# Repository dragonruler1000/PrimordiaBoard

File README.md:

</br>
# [Primordiaboard](https://primordiasystems.minecraftchest2.us/projects/primordiaboard.html)

Hello! This is my submission for Hackpad! It was made for Hackpad v3.

## Features
- A big 0.91" OLED screen
- Some custom silkscreen art
- 12 full MX-style keyswitches
- KMK firmware support!

## PCB

Here are pictures of my PCB:

| **Schematic** | **PCB** |
|---------------|---------|
|  |  |

✅ DRC was run with **0 errors**

## CAD

Designed using **FreeCAD** and **TinkerCAD** (it was painful...).

The case fits together with 4x M3 screws and bolts.

## Firmware

The firmware is written in **KMK** and included in this repo.

> ⚠️ There may be additional setup required for KMK—see [KMK Docs](https://kmkfw.io/docs/) for more info.

## Bill of Materials (BOM)
- 1x Seeed XIAO RP2040
- 12x MX-style keyswitches
- 12x 1N4148 diodes
- 1x SSD1306 128x32 OLED (5V VCC, 3.3V logic, I2C)
- 4x M3x16mm screws
- 4x M3 heat-set inserts (5mm x 4mm)
- 1x 3D printed

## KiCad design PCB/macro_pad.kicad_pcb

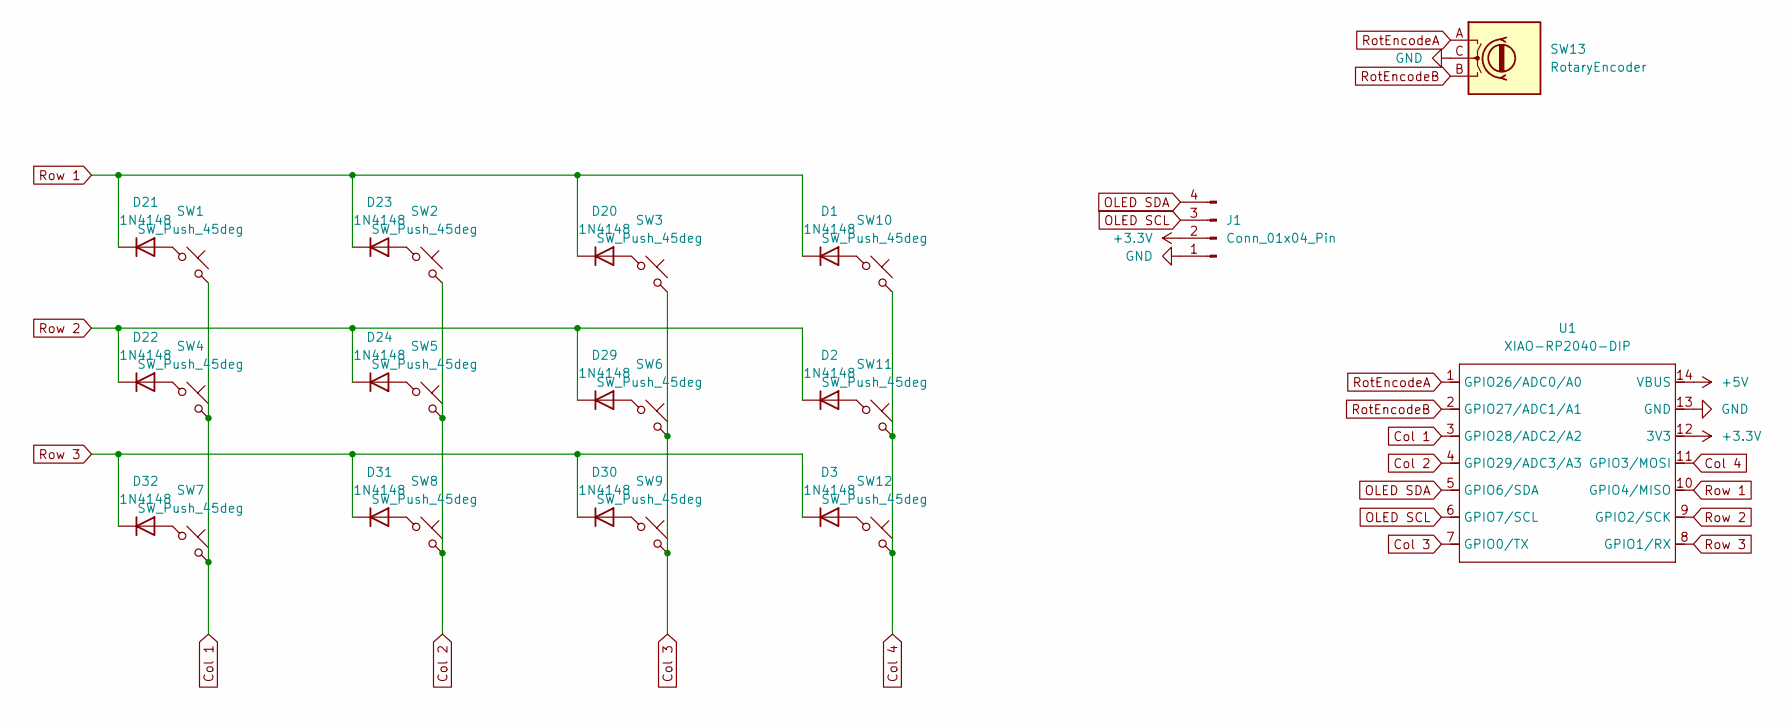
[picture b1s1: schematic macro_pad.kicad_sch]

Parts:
D1, D2, D3, D20, D21, D22, D23, D24, D29, D30, D31, D32: 1N4148; D_DO-35_SOD27_P7.62mm_Horizontal
J1: Conn_01x04_Pin; SSD1306-0.91-OLED-4pin-128x32
SW1, SW2, SW3, SW4, SW5, SW6, SW7, SW8, SW9, SW10, SW11, SW12: SW_Push_45deg; SW_Cherry_MX_1.00u_PCB
SW13: RotaryEncoder; RotaryEncoder_Alps_EC11E_Vertical_H20mm
U1: XIAO-RP2040-DIP

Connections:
+3.3V: J1.2, U1.12 (3V3)
+5V: U1.14 (VBUS)
Col 1: SW1.2, SW4.2, SW7.2, U1.3 (GPIO28/ADC2/A2)
Col 2: SW2.2, SW5.2, SW8.2, U1.4 (GPIO29/ADC3/A3)
Col 3: SW3.2, SW6.2, SW9.2, U1.7 (GPIO0/TX)
Col 4: SW10.2, SW11.2, SW12.2, U1.11 (GPIO3/MOSI)
GND: J1.1, SW13.C, U1.13 (GND)
unnamed: D1.2 (A), SW10.1
unnamed: D2.2 (A), SW11.1
unnamed: D3.2 (A), SW12.1
unnamed: D20.2 (A), SW3.1
unnamed: D21.2 (A), SW1.1
unnamed: D22.2 (A), SW4.1
unnamed: D23.2 (A), SW2.1
unnamed: D24.2 (A), SW5.1
unnamed: D29.2 (A), SW6.1
unnamed: D30.2 (A), SW9.1
unnamed: D31.2 (A), SW8.1
unnamed: D32.2 (A), SW7.1
OLED SCL: J1.3, U1.6 (GPIO7/SCL)
OLED SDA: J1.4, U1.5 (GPIO6/SDA)
RotEncodeA: SW13.A, U1.1 (GPIO26/ADC0/A0)
RotEncodeB: SW13.B, U1.2 (GPIO27/ADC1/A1)
Row 1: D1.1 (K), D20.1 (K), D21.1 (K), D23.1 (K), U1.10 (GPIO4/MISO)
Row 2: D2.1 (K), D22.1 (K), D24.1 (K), D29.1 (K), U1.9 (GPIO2/SCK)
Row 3: D3.1 (K), D30.1 (K), D31.1 (K), D32.1 (K), U1.8 (GPIO1/RX)

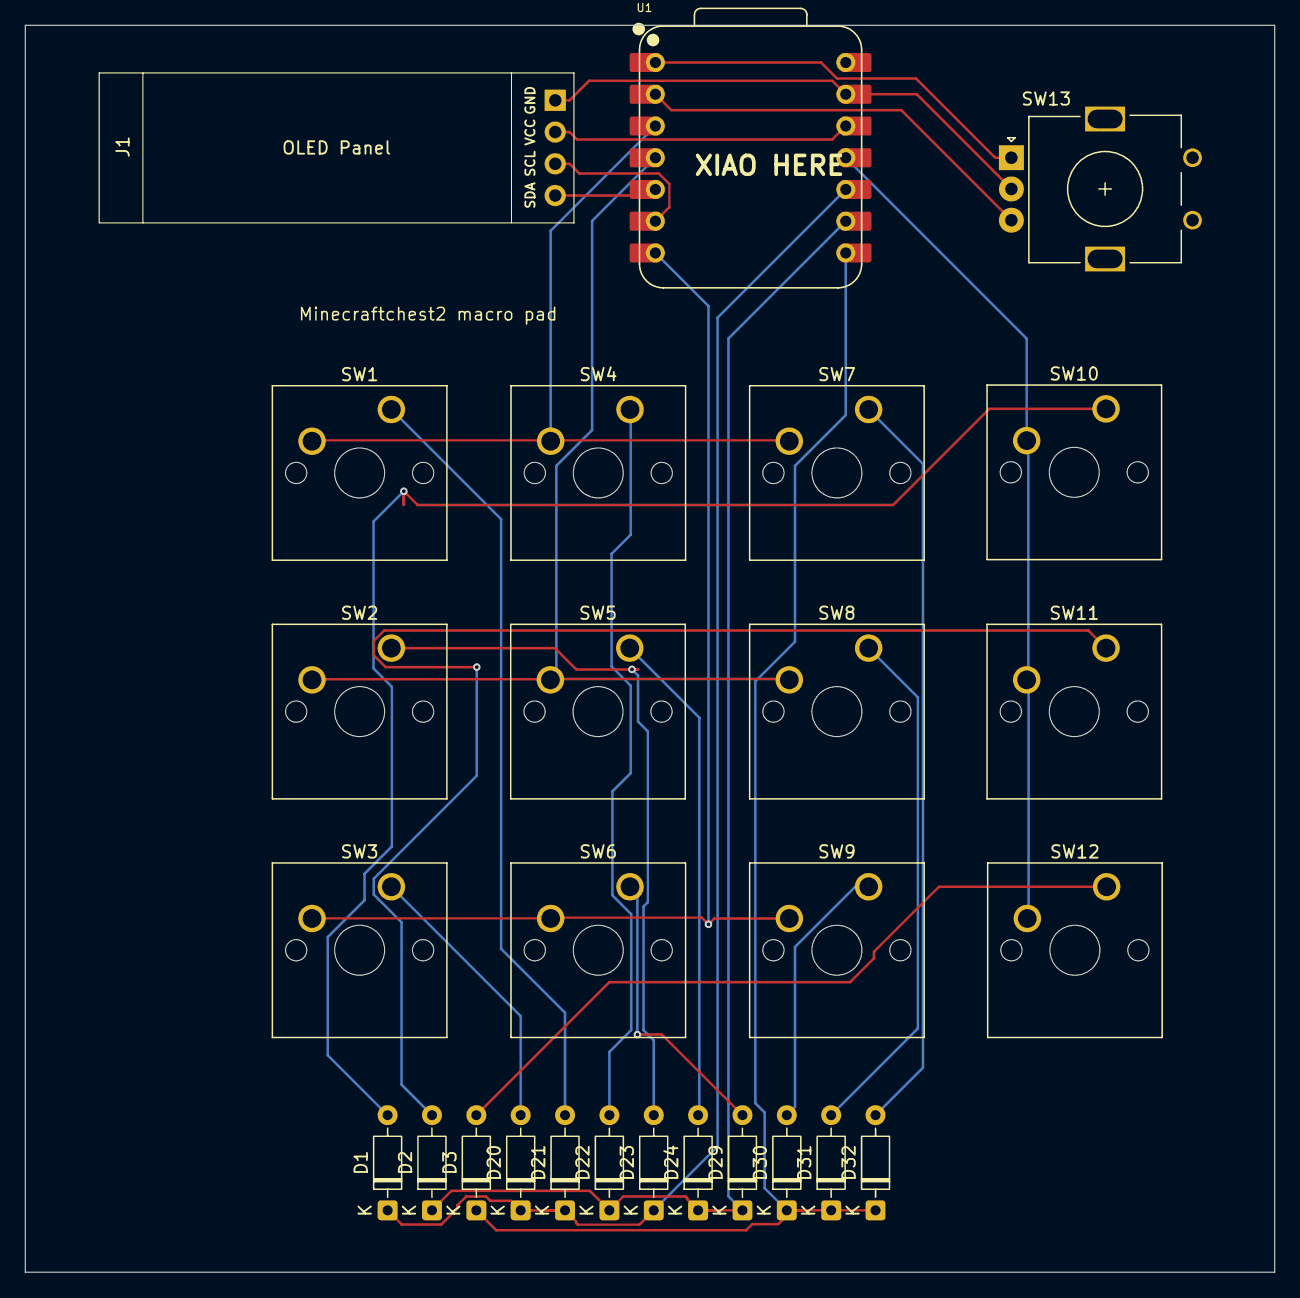
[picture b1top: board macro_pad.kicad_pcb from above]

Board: 2 copper layers, 100.0 x 99.8 mm, 27 parts (0 on the bottom side), 25 nets.

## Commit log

2025-06-07 Started laying out PCB
2025-06-07 Got the traces routed
2025-06-07 adding silk screen and created the gerbers
2025-06-07 added a stl and step version of the pcb
2025-06-10 Got the case for the PCB made
2025-06-14 making sure the case is how i need it.
2025-06-14 adding updated screenshots for the readme
2025-06-15 making sire the needed files are added and unneed files where removed
2025-06-15 adding the firmware for the hackpad
2025-06-15 adding the files to the proper places
2025-06-15 Create README.md
    Need to finish updating it to work with my keyboard
2025-06-15 Update README.md
    Got the README to match my macropad
2025-06-15 Update README.md
    added a link to my arg site
2025-06-19 Update README.md
    adding view counter
2025-06-19 Update README.md
    update counter link
